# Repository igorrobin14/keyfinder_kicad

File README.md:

# Séance 5 de Design : modélisation sur KiCad 7.0 du circuit imprimé d'un keyfinder de chez Action

## Igor Robin - ZZ2 - F1

### Contenu du dépôt
- ```diagramme_originel.png``` et ```diagramme_modifie.pdf``` - Diagramme donné à titre d'exemple en cours et diagramme complété avec d'autres fonctionnalités
- Les fichiers KiCad 7.0 correspondant au shématique, au circuit imprimé, ainsi qu'au projet lui-même
- La sheet du Development Kit (PCA10040) de Nordic Semiconductors (PCA10040_Schematic_And_PCB.pdf)
- Une photo du schématique
- Un photo du circuit imprimé
- Une vue 3D
- Ce ```README.md```

###
*Utilisation : télécharger le dépôt complet, extraire l'archive .zip, mettre tous les fichiers qu'elle contient dans un dossier choisi, mettre au même niveau que le ficher projet (.kicad_pro) le dépôt complet qui se trouve à cette adresse :*
https://github.com/NordicPlayground/nrf5-eagle-reference-design
*Ouvrir le projet dans KiCad et faire en sorte que le package nRF52832 soit prit en compte*

## Introduction
Le but de cette séance de Design était de modéliser sur KiCad 7.0 le circuit imprimé contenu dans le keyfinder de chez Action. Au préalable, il fallait élaborer un diagramme inspiré de celui montré en cours présentant les fonctionnalités du circuit imprimé et notamment quels sont les composants présents et par quels pins ils sont reliés au SoC. Par la suite, il fallait associer les composants avec leurs empreintes et trouver des composants répondant aux besoins. Enfin, il fallait prendre soin de router correctement les composants sur KiCad afin d'assurer leur fonctionnement.

## Mise en œuvre
Afin de trouver les composants requis, la méthode utilisée a été celle-ci : chercher une empreinte sur KiCad pour chaque composant (un epreinte qui mentionne une référence complète et un fabricant), aller voir grâce au moteur de recherche de composants Octopart si le composant répondait aux besoins et s'il était disponible sur des sites courants (DigiKey, Farnell, Mouser), et si c'était le cas, associer l'empreinte au composant.

De plus, les critères de sélection étaient les suivants :
- Le composant est-il disponible sur les principaux sites web ?
- Le composant a-t-il des dimensions acceptables ? (taille raisonnable, au maximum 12mm sur sa plus grande dimensions, sauf pour la pile)
- A t-il les bonnes caractéristiques techniques ? (*Travail réalisé par un débutant et donc susceptible de contenir des erreurs, des confusions de termes et des points oubliés, notamment à ce niveau là*)

## LED
La LED choisie est une IN-PI554FCH de chez Inolux. Comme nous pouvons le voir, sur le schématique, elle est reliée à la masse d'un côté et a une resistance de l'autre, la résistance étant reliée au pin P0.12 du SoC. Le SoC alimente donc la LED directement. Au niveau des caractéristiques techniques, la datasheet de la LED indique qu'elle fonctionne entre 1.8V et 3.3V, or le SoC fonctionne également à ce niveau de tension, et donc cette LED a été retenue.

## Boutons
Les boutons choisis sont des EVQPUJ02K de chez Panasonic. Le raisonnement a été le suivant : le bouton 1 (voir schématique), lorsqu'il est pressé, doit envoyer un signal au SoC, et le SoC doit décider ensuite d'allumer la LED et de déclencher le buzzer. Le bouton 1 est donc branché d'un côté à l'alimentation provenant de la pile, et de l'autre côté à un pin du SoC (ici le pin P0.15).

## Reset et JTAG
Grâce notamment à l'aide d'un ami lors d'un évènement IsiLabs (club d'informatique de l'ISIMA), le système suivant a été mit en place : un connecteur de programmation de type JTAG a été utilisé. Sur celui-ci, on relie le VCC à l'alimentation provenant de la pile, le GND à la masse, on laisse le SWO flottant, on relie le SWDIO au SWDIO du SoC (pin SWDIO @26), le SWCLK au pin SWCLK@25 du SoC et le RESET au pin P0.21/RESET du SoC. Le fil reliant les deux RESET est aussi connecté à l'alimentation en passant par une résistance et à un bouton qui, lorsqu'il est actionné, fait qu'un 0 logique est envoyé au niveau du RESET, ce qui le déclenche. Les sources d'inspiration pour ce mécanisme ont été les feuilles de dessin du Development Kit (PCA10040), disponibles en .pdf dans le dépôt (voir Interface MCU Programming Connector sur la Sheet 4 et Reset switch sur la Sheet 2). Il est a noté que dans la Sheet 4 le connecteur utilisé est un TC2050-IDC, or celui présent sur le schématique est un TC2030-IDC, mais étant donné que le principe de fonctionnement est le même, le choix de celui-ci a été fait. De plus, le TC2050-IDC n'était pas disponible de base dans KiCad.

## Buzzer
Le buzzer choisi est un AST1109MLTRQ de chez Mallory, celui-ci est relié d'un côté au pin P0.03 du SoC et de l'autre côté à la masse. Le SoC aliment donc directement le buzzer quand il le décide (en général après qu'on ait appuyé sur le bouton 1).

## Pile
La pile choisie est une CR2032, pour rester fidèle au keyfinder. Sur KiCad, il s'agit de la modélisation du battery holder qui est effectuée, qui est un 1057 de chez Keystone. Un grand trou est ainsi visible sur le circuit imprimé ou ce holder est censé s'incruster et accueillir la pile.

## Antenne
Il a été choisi de rajouter une antenne PRO-OB-440 de chez Abracon connectée directement au pin P0.27 du SoC qui est donc alimentée dès lors que le SoC le décide et qui est notamment Bluetooth.

## Résistances
Les résistances choisies sont des WSKW06123L000FEA de chez Vishay. Il est a noté que la résistance utilisée au niveau du RESET n'a pas une valeur correcte puisque selon la sheet elle doit être de 18k Ohms.

Les références exactes des composants sont marquées sur le schématique.

## Concepts à éclaircir et questions
- Le branchement du JTAG est-il correct ?
- Le SoC peut-il alimenter à la fois le buzzer et la LED ?
- Le routage est-il correct ? Par exemple, le SoC est-il alimenté correctement puisque les VDD ont l'air d'être reliés à SWDCLK ?
- A quel point faut-il aller loin dans l'analyse dans caractéristiques techniques et le réalisme concernant les composants ? (ex : faut-il regarder les tensions de fonctionnement, la valeur des résistances, etc ?)
- Comment marche réellement le JTAG, une machine vient se connecter sur le connecteur et programme le SoC ?
- N'y a-t-il pas d'autres composants a rajouter ? Inductances, capacités, résistances qui permettent à ceux rajouter de fonctionner ? Notamment entre l'antenne et le Soc, ou autres ?
- Peut-on directement envoyer un signal au SoC avec le bouton 1 en reliant directement la pile au pin du SoC lorsque le bouton est appuyé ? Y a-t-il un risque de tension trop élevée/faible ?
- Mettre un battery holder sur KiCad est-il correct ? Le grand trou dans le circuit imprimé est-il problématique ?
- (Question de débutant) : différence entre un MCU, un MPU, un SoC, un CPU, un processeur et un micro-contrôleur ?

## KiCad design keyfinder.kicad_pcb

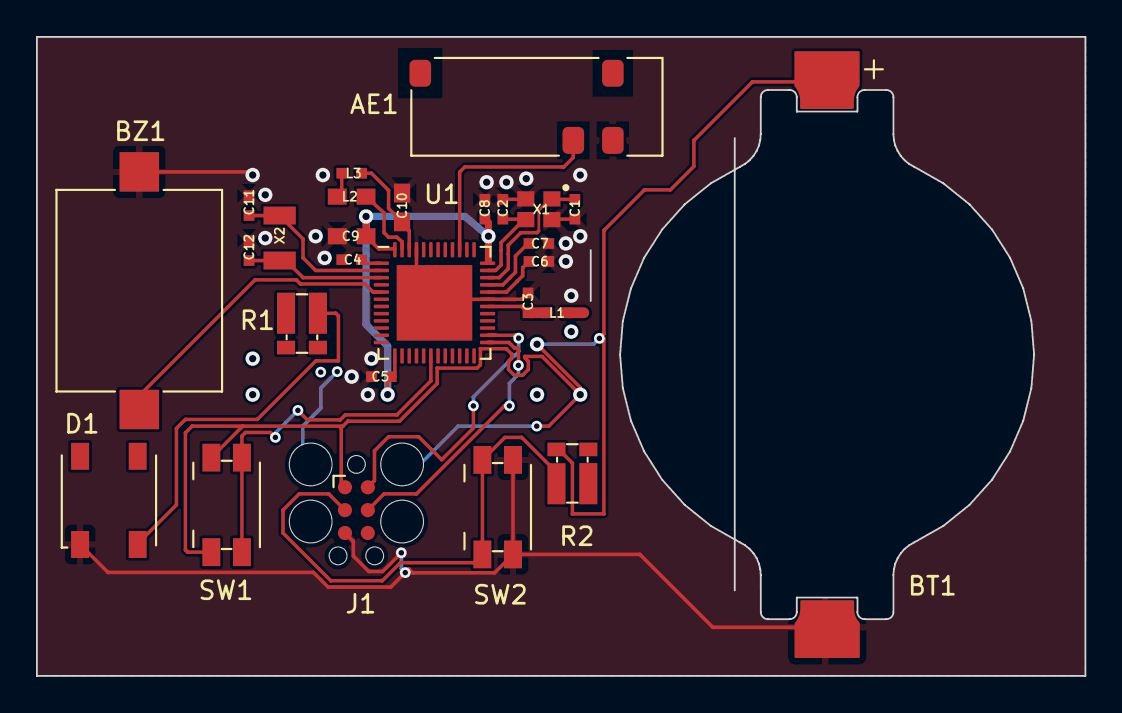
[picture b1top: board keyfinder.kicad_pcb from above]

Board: 2 copper layers, 58.2 x 35.5 mm, 27 parts (0 on the bottom side), 18 nets.

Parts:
AE1: Antenna; Abracon_PRO-OB-440
BT1: Battery_Cell; BatteryHolder_Keystone_1057_1x2032
BZ1: Buzzer; Buzzer_Mallory_AST1109MLTRQ
C1, C2, C11, C12: 12pF; RESC0402_N
C3: 0.8pF; RESC0402_N
C4, C5, C8: 100nF; RESC0402_N
C6: N.M.; RESC0402_N
C7: 100pF; RESC0402_N
C9: 4.7µF; RESC0603_N
C10: 1.0µF; RESC0603_N
D1: LED; LED_Inolux_IN-PI554FCH_PLCC4_5.0x5.0mm_P3.2mm
J1: Conn_ARM_SWD_TagConnect_TC2030; Tag-Connect_TC2030-IDC-FP_2x03_P1.27mm_Vertical
L1: 3.9nH; RESC0402_N
L2: 10µH; RESC0603_N
L3: 15nH; RESC0402_N
R1, R2: 75; R_Shunt_Vishay_WSKW0612
SW1, SW2: SW_Push; Panasonic_EVQPUJ_EVQPUA
U1: NRF52832; QFN-48-1EP_6x6mm_P0.4mm_EP4.2x4.2mm
X1: 32MHz; BT-XTAL_2016_N
X2: 32.768kHz; XTAL_3215_N

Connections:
/P0.03: BZ1.1 (-), U1.5 (P0.03/AIN1@05)
/P0.10: C10.1, L3.2
/P0.12: R1.2, U1.15 (P0.12@15)
/P0.15: SW1.2, U1.18 (P0.15@18)
/P0.27: AE1.1 (A), U1.39 (P0.27@39)
/SWDCLK: J1.4 (SWCLK), U1.25 (SWDCLK@25)
/SWDIO: J1.2 (SWDIO), U1.26 (SWDIO@26)
ANT: C1.1, X1.1
DEC2: C2.1, X1.3
DEC3: C3.1, L1.1
GND: BT1.2 (-), BZ1.2 (+), C1.2, C2.2, C3.2, C4.2, C5.2, C6.2, C7.2, C8.2, C9.2, C10.2, C11.1, C12.1, D1.1 (K), J1.5 (GND), SW2.2, U1.31 (VSS@31), U1.45 (VSS@45), X1.2, X1.4
unnamed: C4.1, D1.2 (A), R1.1
unnamed: J1.3 (~RESET), R2.1, SW2.1, U1.24 (P0.21/RESET@24)
P0.10: L2.2, L3.1
P0.20: C11.2, X2.1
P0.21/RESET: C12.2, X2.2
SWDCLK: C5.1, C8.1, C9.1
VCC: BT1.1 (+), J1.1 (VCC), R2.2, SW1.1, U1.13 (VDD@13), U1.36 (VDD@36), U1.48 (VDD@48)

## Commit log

2023-11-23 Première version
    Première version du circuit imprimé
2023-11-23 Diagrammes
    Ajout du diagramme originel et du diagramme modifié
2023-11-23 Ajout de fichiers complémentaires
    Ajout du README.md, de la sheet du DK, et de photos utiles
2023-11-23 Modification du README.md
2023-11-23 Question finale
2023-11-23 Mise en forme 1
2023-11-23 Question sur le battery holder
2023-11-23 Différences entre certains termes
